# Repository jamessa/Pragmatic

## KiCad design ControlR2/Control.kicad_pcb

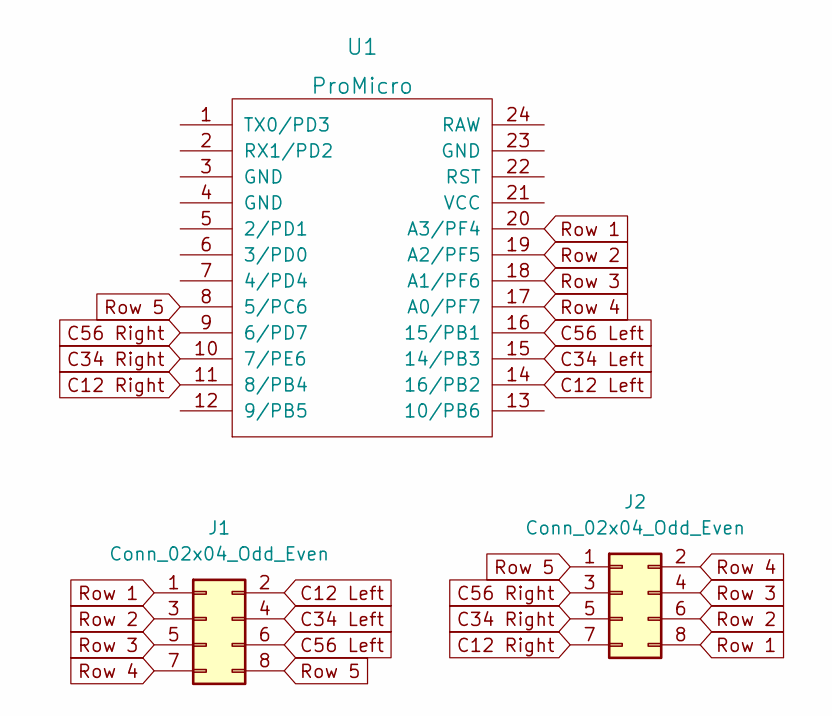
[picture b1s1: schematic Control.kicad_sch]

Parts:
J1, J2: Conn_02x04_Odd_Even; matrix_connector
U1: ProMicro; ProMicro Reversed

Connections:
C12 Left: J1.2, U1.14 (16/PB2)
C12 Right: J2.7, U1.11 (8/PB4)
C34 Left: J1.4, U1.15 (14/PB3)
C34 Right: J2.5, U1.10 (7/PE6)
C56 Left: J1.6, U1.16 (15/PB1)
C56 Right: J2.3, U1.9 (6/PD7)
Row 1: J1.1, J2.8, U1.20 (A3/PF4)
Row 2: J1.3, J2.6, U1.19 (A2/PF5)
Row 3: J1.5, J2.4, U1.18 (A1/PF6)
Row 4: J1.7, J2.2, U1.17 (A0/PF7)
Row 5: J1.8, J2.1, U1.8 (5/PC6)

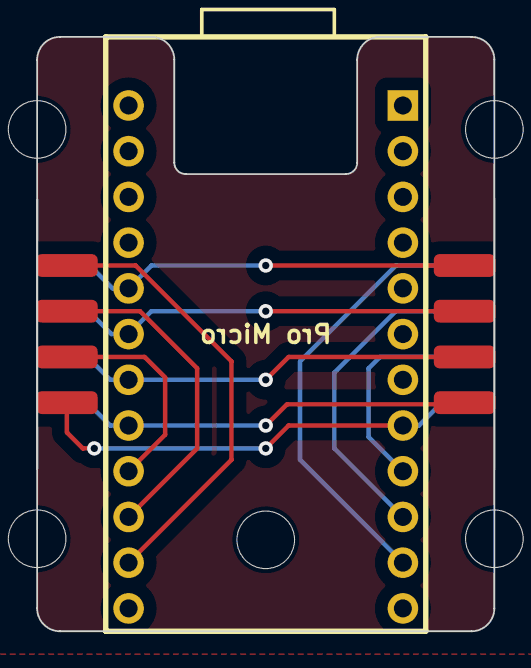
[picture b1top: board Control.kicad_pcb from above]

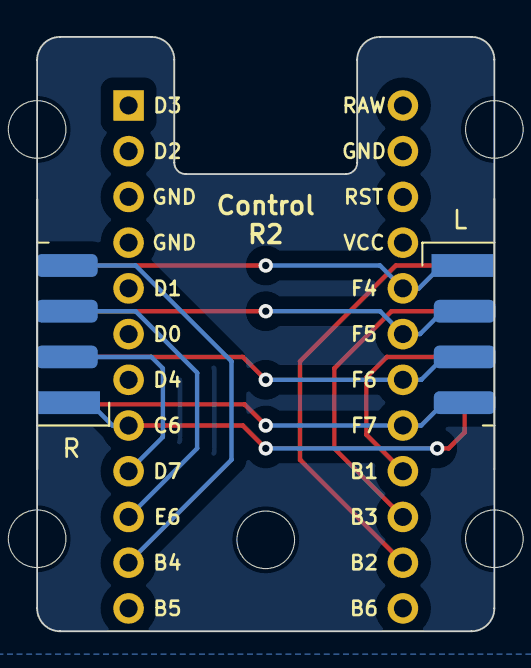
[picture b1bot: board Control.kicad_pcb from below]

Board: 2 copper layers, 25.4 x 33.0 mm, 3 parts (3 on the bottom side), 11 nets.

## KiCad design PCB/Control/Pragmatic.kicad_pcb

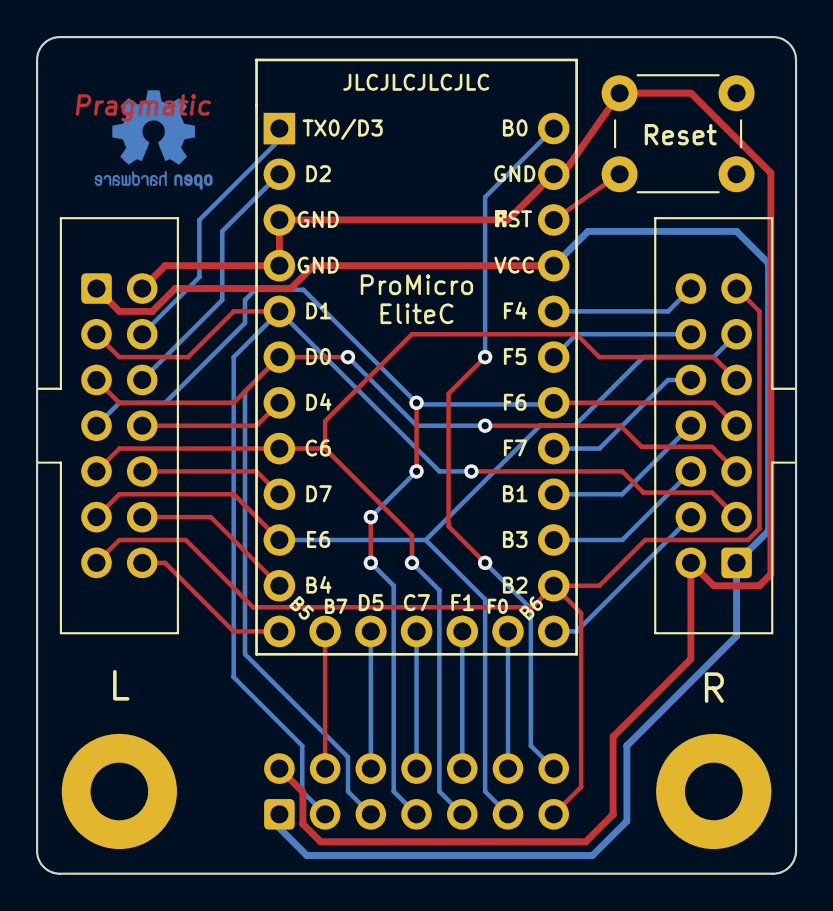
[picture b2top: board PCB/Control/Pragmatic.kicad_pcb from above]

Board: 2 copper layers, 42.2 x 46.5 mm, 9 parts (1 on the bottom side), 27 nets.

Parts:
J1: L; IDC-Header_2x07_P2.54mm_Vertical
J2: R; IDC-Header_2x07_P2.54mm_Vertical
J3: M; IDC-Header_2x07_P2.54mm_Vertical
L1: JLC Legend
Logo1: OSHW-Logo2_7.3x6mm_Copper
M1, M2: MountingHole_3.2mm_M3_Pad
SW1: SW_Push; SW_PUSH_6mm
U1: ProMicro/Elite-C; Elite-C

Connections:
Col1: J1.4, U1.1 (TX0/PD3)
Col2: J1.6, U1.2 (RX1/PD2)
Col3: J1.8, U1.7 (4/PD4)
Col4: J1.10, U1.9 (6/PD7)
Col5: J1.12, U1.11 (8/PB4)
Col6: J1.14, U1.12 (9/PB5)
Col7: J2.4, U1.13 (10/PB6)
Col8: J2.6, U1.15 (14/PB3)
Col9: J2.8, U1.16 (15/PB1)
Col10: J2.10, U1.17 (A0/PF7)
Col11: J2.12, U1.19 (A2/PF5)
Col12: J2.14, U1.20 (A3/PF4)
Col13: J3.4, U1.25 (B7)
Col14: J3.6, U1.26 (D5)
Col15: J3.8, U1.27 (C7)
Col16: J3.10, U1.28 (F1)
Col17: J3.12, U1.29 (F0)
Col18: J3.14, U1.24 (B0)
GND: J1.2, J2.2, J3.2, SW1.2, U1.3 (GND), U1.4 (GND), U1.23 (GND)
Reset: SW1.1, U1.22 (RST)
Row1: J1.3, J2.3, J3.3, U1.5 (2/PD1)
Row2: J1.5, J2.5, J3.5, U1.6 (3/PD0)
Row3: J1.7, J2.7, J3.7, U1.18 (A1/PF6)
Row4: J1.9, J2.9, J3.9, U1.8 (5/PC6)
Row5: J1.11, J2.11, J3.11, U1.10 (7/PE6)
Row6: J1.13, J2.13, J3.13, U1.14 (16/PB2)
VCC: J1.1, J2.1, J3.1, U1.21 (VCC)

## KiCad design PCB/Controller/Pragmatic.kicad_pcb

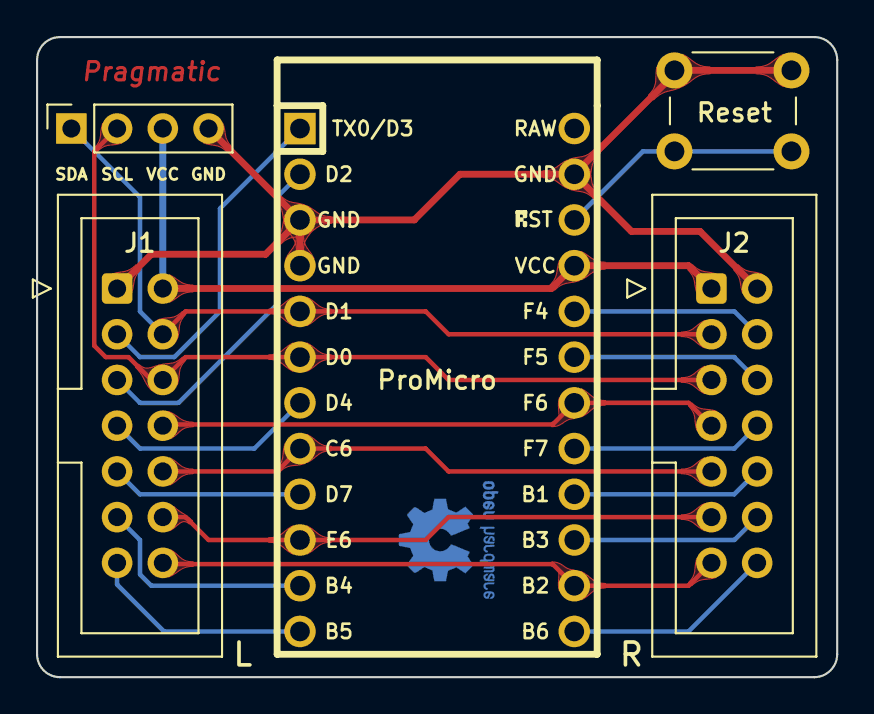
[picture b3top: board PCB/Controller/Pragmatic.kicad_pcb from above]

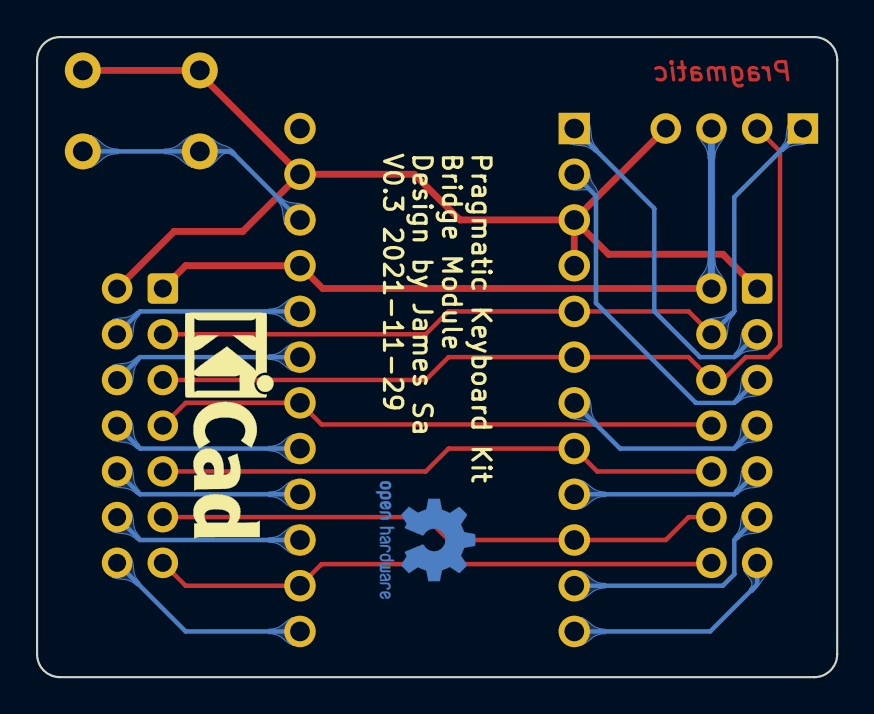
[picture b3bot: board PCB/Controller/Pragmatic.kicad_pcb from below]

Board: 2 copper layers, 44.5 x 35.6 mm, 7 parts (2 on the bottom side), 21 nets.

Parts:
J1: L; IDC-Header_2x07_P2.54mm_Vertical
J2: R; IDC-Header_2x07_P2.54mm_Vertical
J3: Conn_01x04; PinSocket_1x04_P2.54mm_Vertical
Logo1: OSHW-Logo2_7.3x6mm_Copper
Logo2: KiCad-Logo_5mm_SilkScreen
SW1: SW_Push; SW_PUSH_6mm
U1: ProMicro; ArduinoProMicro

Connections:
Col1: J1.3, U1.1
Col2: J1.5, U1.2
Col3: J1.7, U1.7
Col4: J1.9, U1.9
Col5: J1.11, U1.11
Col6: J1.13, U1.12
Col7: J2.14, U1.13
Col8: J2.12, U1.15
Col9: J2.10, U1.16
Col10: J2.8, U1.17
Col11: J2.6, U1.19
Col12: J2.4, U1.20
GND: J1.1, J2.2, J3.4, SW1.2, U1.3, U1.4, U1.23
Reset: SW1.1, U1.22
Row1: J1.4, J2.3, J3.1, U1.5
Row2: J1.6, J2.5, J3.2, U1.6
Row3: J1.8, J2.7, U1.18
Row4: J1.10, J2.9, U1.8
Row5: J1.12, J2.11, U1.10
Row6: J1.14, J2.13, U1.14
VCC: J1.2, J2.1, J3.3, U1.21

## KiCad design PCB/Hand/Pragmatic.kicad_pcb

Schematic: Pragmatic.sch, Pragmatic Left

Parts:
D1, D2, D3, D4, D5, D6, D7, D8, D9, D10, D11, D12, D13, D14, D15, D16, D17, D18, D19, D20, D21, D22, D23, D24, D25, D26, D27, D28, D29, D30, D31, D32, D33, D34, D35, D36: D; D_SMD_With_Shadow; LCSC C81598
D37: LED; LED_0805_With_Shadow; LCSC C2297
H1, H2, H3, H4: MountingHole; MountingHole_3.2mm_M3_DIN965_Pad_TopBottom
J1: Conn_02x08_Odd_Even; IDC-Header_2x08_P2.54mm_Vertical_Mirrored; LCSC C3406
J2: Conn_01x04; PinSocket_1x04_P2.54mm_Vertical
R1: R; R_0805_With_Shadow; LCSC C17408
SW1, SW2, SW3, SW4, SW5, SW6, SW7, SW8, SW9, SW10, SW11, SW12, SW13, SW19, SW25, SW31, SW32, SW33, SW34, SW35, SW36: SW_Push; Switch_1u_Mirrored
SW14: Q; Switch_1u_Mirrored
SW15: W; Switch_1u_Mirrored
SW16: E; Switch_1u_Mirrored
SW17: R; Switch_1u_Mirrored
SW18: T; Switch_1u_Mirrored
SW20: A; Switch_1u_Mirrored
SW21: S; Switch_1u_Mirrored
SW22: D; Switch_1u_Mirrored
SW23: F; Switch_1u_Mirrored
SW24: G; Switch_1u_Mirrored
SW26: Z; Switch_1u_Mirrored
SW27: X; Switch_1u_Mirrored
SW28: C; Switch_1u_Mirrored
SW29: V; Switch_1u_Mirrored
SW30: B; Switch_1u_Mirrored

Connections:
Col1: J1.5, SW1.2, SW7.2, SW13.2, SW19.2, SW25.2, SW31.2
Col2: J1.7, SW2.2, SW8.2, SW14.2, SW20.2, SW26.2, SW32.2
Col3: J1.9, SW3.2, SW9.2, SW15.2, SW21.2, SW27.2, SW33.2
Col4: J1.11, SW4.2, SW10.2, SW16.2, SW22.2, SW28.2, SW34.2
Col5: J1.13, SW5.2, SW11.2, SW17.2, SW23.2, SW29.2, SW35.2
Col6: J1.15, SW6.2, SW12.2, SW18.2, SW24.2, SW30.2, SW36.2
GND: D37.1 (K), J1.1, J2.4
unnamed: D1.2 (A), SW1.1
unnamed: D2.2 (A), SW2.1
unnamed: D3.2 (A), SW3.1
unnamed: D4.2 (A), SW4.1
unnamed: D5.2 (A), SW5.1
unnamed: D6.2 (A), SW6.1
unnamed: D7.2 (A), SW7.1
unnamed: D8.2 (A), SW8.1
unnamed: D9.2 (A), SW9.1
unnamed: D10.2 (A), SW10.1
unnamed: D11.2 (A), SW11.1
unnamed: D12.2 (A), SW12.1
unnamed: D13.2 (A), SW13.1
unnamed: D14.2 (A), SW14.1
unnamed: D15.2 (A), SW15.1
unnamed: D16.2 (A), SW16.1
unnamed: D17.2 (A), SW17.1
unnamed: D18.2 (A), SW18.1
unnamed: D19.2 (A), SW19.1
unnamed: D20.2 (A), SW20.1
unnamed: D21.2 (A), SW21.1
unnamed: D22.2 (A), SW22.1
unnamed: D23.2 (A), SW23.1
unnamed: D24.2 (A), SW24.1
unnamed: D25.2 (A), SW25.1
unnamed: D26.2 (A), SW26.1
unnamed: D27.2 (A), SW27.1
unnamed: D28.2 (A), SW28.1
unnamed: D29.2 (A), SW29.1
unnamed: D30.2 (A), SW30.1
unnamed: D31.2 (A), SW31.1
unnamed: D32.2 (A), SW32.1
unnamed: D33.2 (A), SW33.1
unnamed: D34.2 (A), SW34.1
unnamed: D35.2 (A), SW35.1
unnamed: D36.2 (A), SW36.1
unnamed: D37.2 (A), R1.2
Row1: D1.1 (K), D2.1 (K), D3.1 (K), D4.1 (K), D5.1 (K), D6.1 (K), J1.6
Row2: D7.1 (K), D8.1 (K), D9.1 (K), D10.1 (K), D11.1 (K), D12.1 (K), J1.8
Row3: D13.1 (K), D14.1 (K), D15.1 (K), D16.1 (K), D17.1 (K), D18.1 (K), J1.10
Row4: D19.1 (K), D20.1 (K), D21.1 (K), D22.1 (K), D23.1 (K), D24.1 (K), J1.12
Row5: D25.1 (K), D26.1 (K), D27.1 (K), D28.1 (K), D29.1 (K), D30.1 (K), J1.14
Row6: D31.1 (K), D32.1 (K), D33.1 (K), D34.1 (K), D35.1 (K), D36.1 (K), J1.16
SCL: J1.3, J2.2
SDA: J1.4, J2.1
VCC: J1.2, J2.3, R1.1

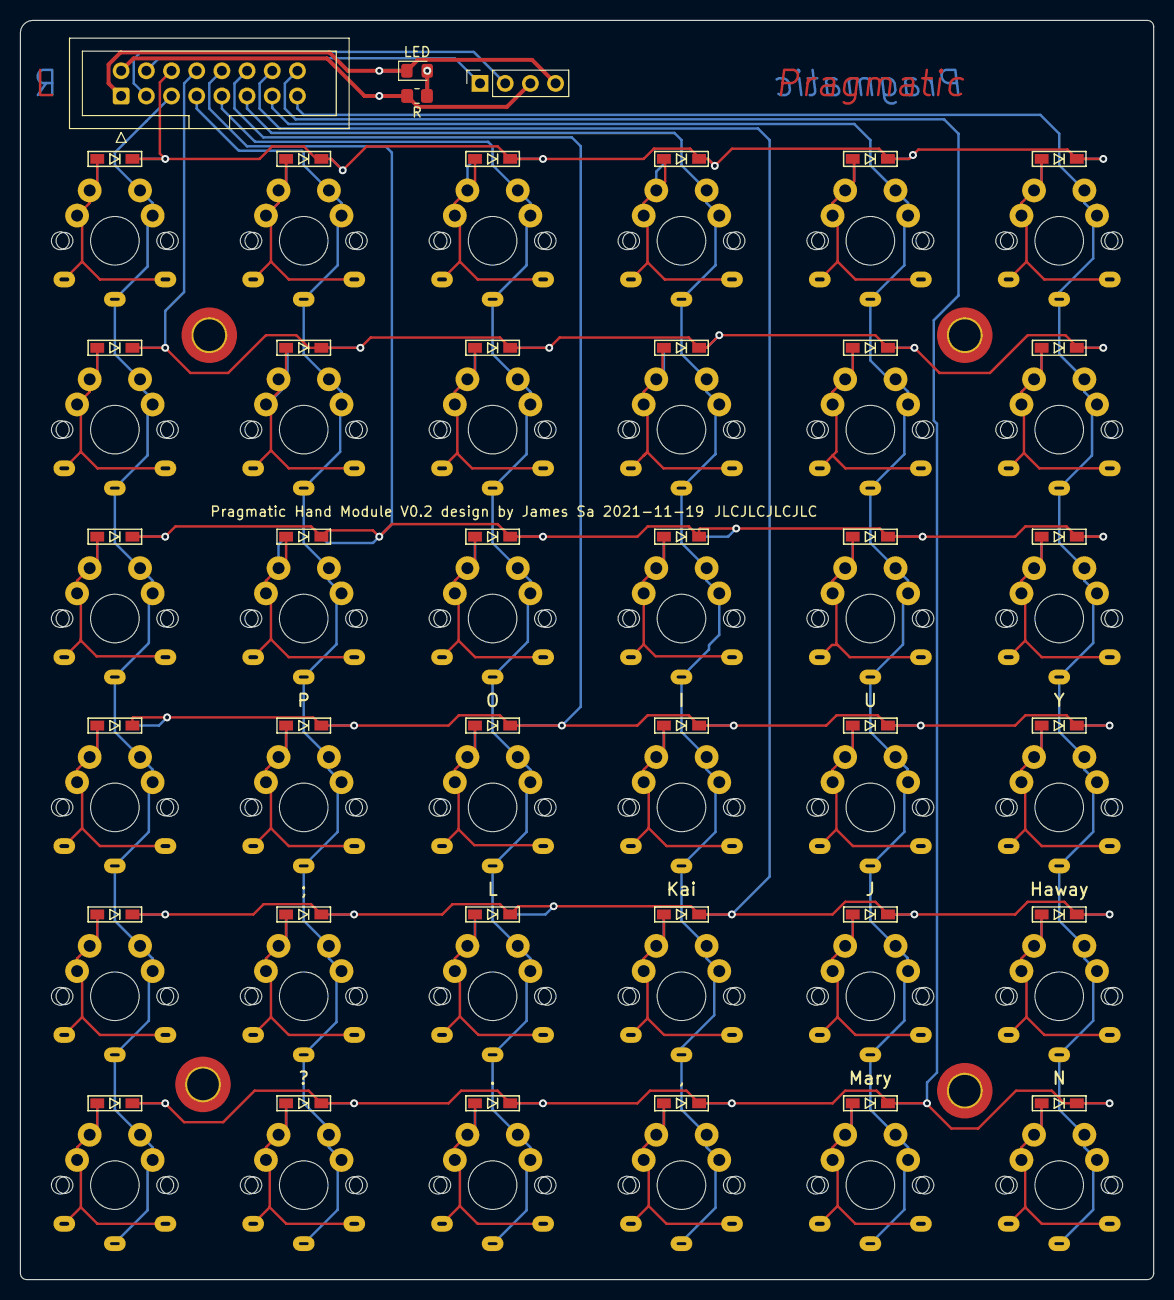
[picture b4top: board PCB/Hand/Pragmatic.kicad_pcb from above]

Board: 2 copper layers, 114.3 x 127.0 mm, 80 parts (0 on the bottom side), 53 nets.

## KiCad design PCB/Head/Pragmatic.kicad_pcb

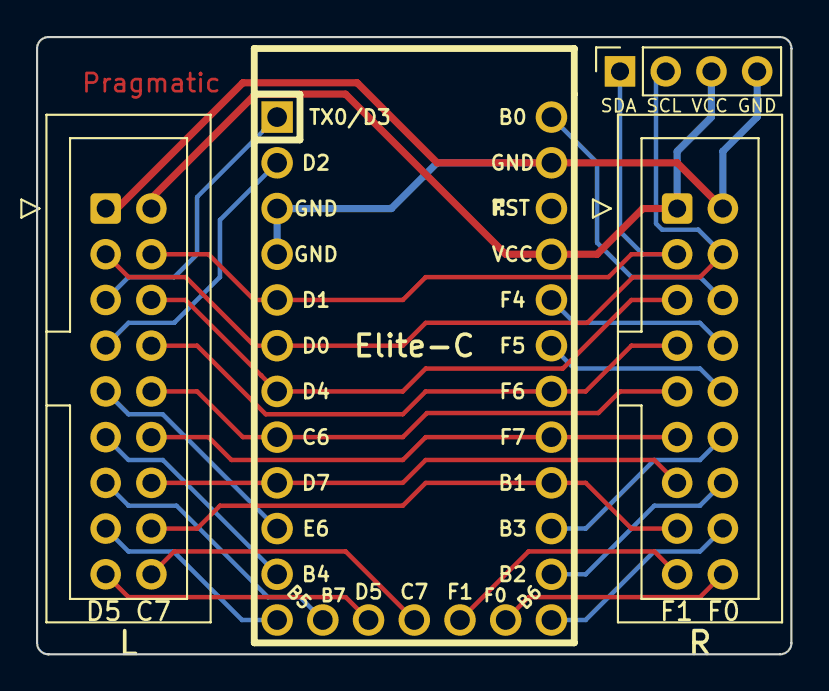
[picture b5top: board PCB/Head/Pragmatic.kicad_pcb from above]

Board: 2 copper layers, 41.9 x 34.3 mm, 6 parts (0 on the bottom side), 26 nets.

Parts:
J1: L; IDC-Header_2x08_P2.54mm_Vertical
J2: R; IDC-Header_2x08_P2.54mm_Vertical
J3: Conn_01x04; PinSocket_1x04_P2.54mm_Vertical
J4, J5: Conn_01x02_Male; PinHolder_1x02_P2.54mm_Vertical
U1: Elite-C

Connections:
Col1: J1.5, U1.1
Col2: J1.7, U1.2
Col3: J1.9, U1.10
Col4: J1.11, U1.11
Col5: J1.13, U1.25
Col6: J1.15, U1.12
Col7: J2.16, U1.13
Col8: J2.14, U1.14
Col9: J2.12, U1.15
Col10: J2.10, U1.19
Col11: J2.8, U1.20
Col12: J2.6, U1.24
GND: J1.1, J2.2, J3.4, U1.3, U1.4, U1.23
unnamed: J4.1, U1.26
unnamed: J4.2, U1.27
unnamed: J5.1, U1.28
unnamed: J5.2, U1.29
Row1: J1.6, J2.5, U1.7
Row2: J1.8, J2.7, U1.18
Row3: J1.10, J2.9, U1.8
Row4: J1.12, J2.11, U1.17
Row5: J1.14, J2.13, U1.9
Row6: J1.16, J2.15, U1.16
SCL: J1.3, J2.4, J3.2, U1.6
SDA: J1.4, J2.3, J3.1, U1.5
VCC: J1.2, J2.1, J3.3, U1.21
